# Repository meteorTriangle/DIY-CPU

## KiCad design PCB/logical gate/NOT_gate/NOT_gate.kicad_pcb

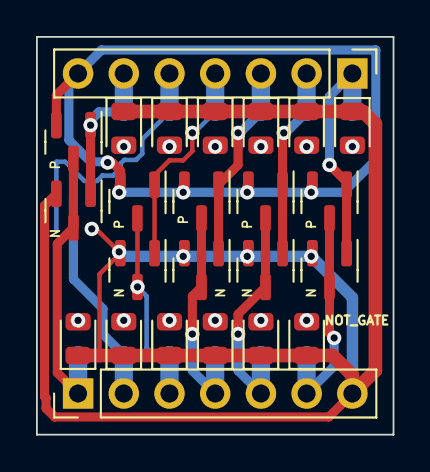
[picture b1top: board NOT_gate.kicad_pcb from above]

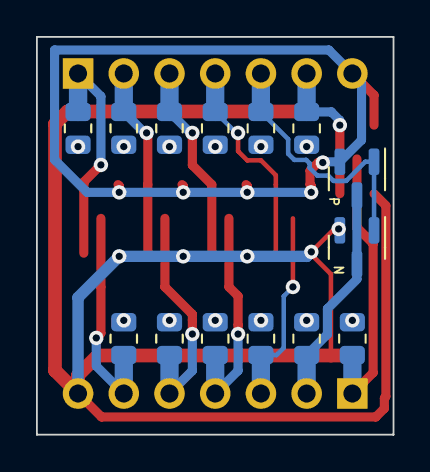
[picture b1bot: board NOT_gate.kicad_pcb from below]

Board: 2 copper layers, 19.8 x 22.1 mm, 38 parts (14 on the bottom side), 26 nets.

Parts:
D1, D2, D3, D4, D5, D6, D7, D8, D9, D10, D11, D12: LED; LED_0805_2012Metric
J1, J2: Conn_01x07; PinHeader_1x07_P2.54mm_Vertical
Q1, Q3, Q5, Q7, Q9, Q11: P; SOT-23
Q2, Q4, Q6, Q8, Q10, Q12: N; SOT-23
R1, R2, R3, R4, R5, R6, R7, R8, R9, R10, R11, R12: R; R_0805_2012Metric

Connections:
+5V: J1.7, Q1.2 (S), Q3.2 (S), Q5.2 (S), Q7.2 (S), Q9.2 (S), Q11.2 (S)
GND: D1.1 (K), D2.1 (K), D3.1 (K), D4.1 (K), D5.1 (K), D6.1 (K), D7.1 (K), D8.1 (K), D9.1 (K), D10.1 (K), D11.1 (K), D12.1 (K), J2.7, Q2.2 (S), Q4.2 (S), Q6.2 (S), Q8.2 (S), Q10.2 (S), Q12.2 (S)
In1: J1.6, Q1.1 (G), Q2.1 (G), R1.1
In2: J1.5, Q5.1 (G), Q6.1 (G), R5.1
In3: J1.4, Q9.1 (G), Q10.1 (G), R9.1
In4: J1.3, Q11.1 (G), Q12.1 (G), R11.1
In5: J1.2, Q3.1 (G), Q4.1 (G), R2.1
In6: J1.1, Q7.1 (G), Q8.1 (G), R6.1
unnamed: D1.2 (A), R1.2
unnamed: D2.2 (A), R2.2
unnamed: D3.2 (A), R3.2
unnamed: D4.2 (A), R4.2
unnamed: D5.2 (A), R5.2
unnamed: D6.2 (A), R6.2
unnamed: D7.2 (A), R7.2
unnamed: D8.2 (A), R8.2
unnamed: D9.2 (A), R9.2
unnamed: D10.2 (A), R10.2
unnamed: D11.2 (A), R11.2
unnamed: D12.2 (A), R12.2
Out1: J2.1, Q1.3 (D), Q2.3 (D), R3.1
Out2: J2.2, Q5.3 (D), Q6.3 (D), R7.1
Out3: J2.3, Q9.3 (D), Q10.3 (D), R10.1
Out4: J2.4, Q11.3 (D), Q12.3 (D), R12.1
Out5: J2.5, Q3.3 (D), Q4.3 (D), R4.1
Out6: J2.6, Q7.3 (D), Q8.3 (D), R8.1

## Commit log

2023-03-08 20230308 1324
2023-03-09 20230309 1854
